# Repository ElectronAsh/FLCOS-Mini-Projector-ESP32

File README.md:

# FLCOS Mini Projector with ESP32 and Composite input.

WARNING: Please do not build this board yet. There are still some checks to do.

UPDATE: 29th April 2023: I finally bought one of the Jakks toy projectors from eBay US.
I hooked up the USB Logic Analyzer to the "SPI" bus on the projector's FLCOS module.
The projector only ever write to three registers after power-up, then another register to enable the FLCOS after a video signal is detected.

So I did a few tweaks to my Arduino code, and now my own board works, too. ;)

I also confirmed that the AliExpress FLCOS modules DO indeed work fine in the Jakks projector, so they are the same/compatible part.

There are still a few issues to sort out, where the FLCOS won't always turn on when you first plug USB power in, but it will work after pulling
the reset (EN_N) Low on the ESP32, or re-flashing via the Arduino IDE.

I've included a few photos below of the projector showing "Gex" on the 3DO.
This is a PAL 3DO, so I tweaked the Arduino code to fit the projected image better.
(the FLCOS registers will default to NTSC, so I tweaked the values for PAL.)

TODO...

Voltage reg pinouts and ADJ pins (use adjustable and add resistor dividers, or look for fixed-output regs for the BOM?)
FPC connector direction, top contact? (The FLCOS module will be mounted upside-down on the board)
Double-check the JST ZH pinout for the LEDs. DONE
Maybe change the pin header to some sort of socket for the Composite input? DONE
Check availability of all ICs on LCSC or Mouser, digikey etc. DONE
Hunt for parts, create a BOM. DONE
Run ERC and DRC. DONE
Order a few test PCBs. DONE

This is a driver board for the FLCOS mini projector modules on AliExpress...
https://www.aliexpress.com/item/1005003386129982.html

There is a forum post here, with the full datasheet for what appears to be the same FLCOS chip used on the AliExpress module.
https://whycan.com/t_2420.html

("datasheet" is actually the product brief. "cps" has all of the register settings.)

The pinout of the lower flex cable on post #4 of the forum seems to match up with the ribbon on the FLCOS module.

The pinout of the RGB LED cable on the module is a bit strange.
There is no correlation between the wire colours, the silkscreen designators, and the RGB LED chip itself.

I tested the RGB LED with a bench PSU, though, and the pinout on the Eagle schematic *should* be correct now.
I just need to double-check that the JST ZH connector for the LED is not rotated 180-degrees or something.

(it's possible the manufacturer changed the RGB LED for a different one on request, which is why the LED cable pinout doesn't seem to tally with the silkscreen?)

The exact maximum LED current is unknown.
I tested one of the Green LEDs with 160mA at first, and it didn't seem to increase in brightness much above 200mA.

The forward voltage drop of the Blue and Green LEDs was around 3.3 Volts, according to my bench PSU (when current-limiting). (there are two Green LEDs on the die) 

The forward voltage drop of the Red LED was around 2.0 Volts.

The included RGB LED has all of Anodes connected together.
I originally put some LM3404 LED driver ICs on the board, but they wouldn't have worked for a common-Anode RGB LED chip, so I changed those for the LM3414 instead.

The FLCOS module appears to be the same one used in the "JAKKS Eyeclops" toy projector...
https://videotechnology.blogspot.com/2010/11/inside-jakks-pacific-eyeclops-mini.html

Before I received some modules, I did a lot of tracing of the JAKKS PCB to try to confirm the pinout against the TVP5150 TV decoder chip.
The pinout seemed to match up with the forum post above.

There was a discussion on Twitter in 2021 about these modules, too...
https://twitter.com/AshEvans81/status/1498184526236987392?s=20&t=zDXLWlJON1HiXY-NYlLocg

The PCB layout was also discussed on the #lab channel of bitluni's Discord server.

bitluni's awesome ESP32 VGA output project was the reason I wanted to add an ESP32 to the board.
It could make for a neat mini movie player or similar (streaming low-res files from SD card.)

https://github.com/bitluni/ESP32Lib/blob/8f4b1bc9c331546c57c1ee837ac37303b8d8739c/examples/VGADemo14Bit/VGADemo14Bit.ino

(bitluni's code is untested with the FLCOS modules atm, but I think it will work OK with a few tweaks. The FLCOS chip accepts video input as sequential R,G,B bytes.)

I kept the TVP5150 chip on the board, as this is the same chip used in the JAKKS projector.
It outputs standard bt.656 style digital video, and accepts Composite input.

(The TVP5150 can receive both NTSC and PAL Composite, using one 14.318 MHz crystal.)

Only the TVP5150 or ESP32 can drive the FLCOS module at any one time.
The TVP chip can set it's output pins to High-Z (this is done via an I2C register), so it should be possible to keep both the ESP32 and TVP5150 onboard.

Most of the footprint libraries for the ESP32, SD slot, TVP5150, and LM3414 were taken from existing open-source projects.
I don't have the names or links to all of those projects now, but I will add them to the README if I can find them.

I used Eagle 9.0.1 to do the PCB layout.

Build at your own risk!

It does finally "work" now, in terms of getting Composite video to display.
But there are a few issues, as mentioned in the update at the top of this README.

I haven't tried generating video on the ESP32 yet, so I'm not 100% sure that will work without PCB changes.

ElectronAsh. ;)

This was a quick test of the Green LEDs. FLCOS chip itself is not powered.

Both Green LEDs in parallel, 220mA, lens was 150mm from the "screen".
The box is only 90mm wide.

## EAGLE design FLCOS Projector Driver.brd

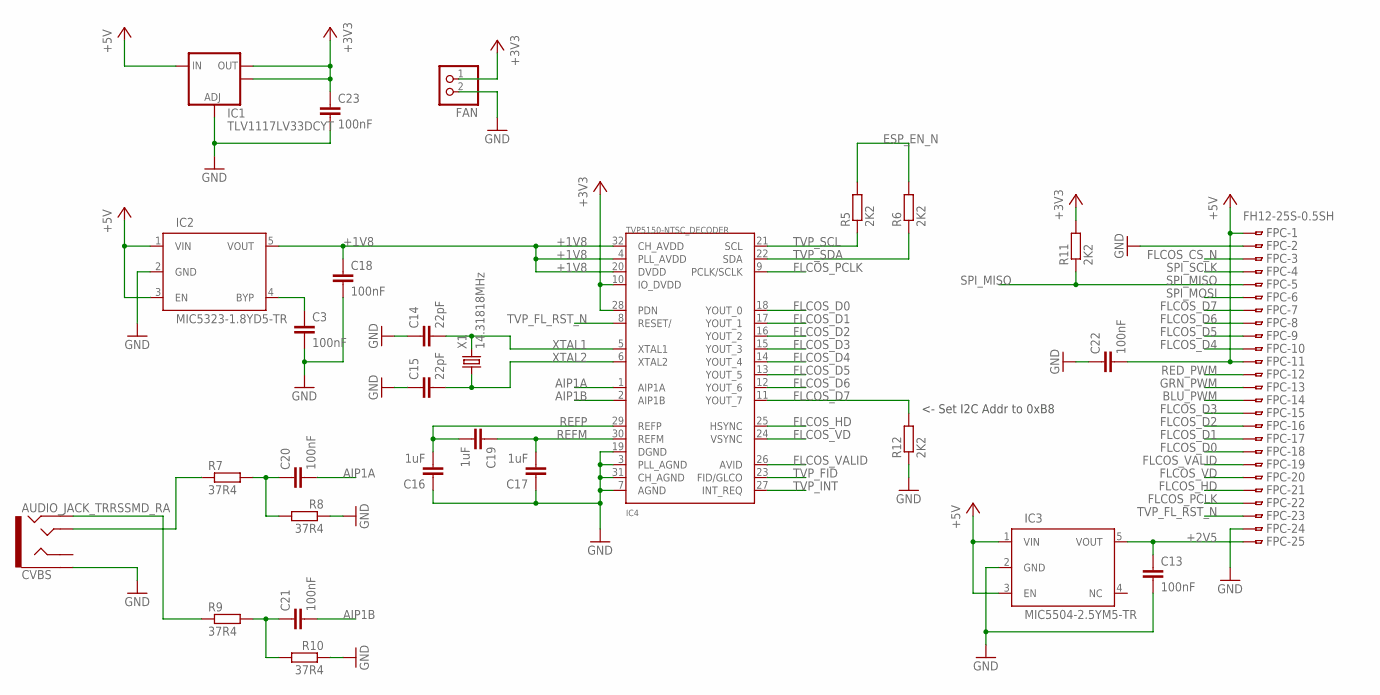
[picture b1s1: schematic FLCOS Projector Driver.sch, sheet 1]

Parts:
C3, C13, C18, C20, C21, C22, C23: 100nF; C0603
C14, C15: 22pF; C0603
C16, C17, C19: 1uF; C0603
CVBS: AUDIO_JACK_TRRSSMD_RA; AUDIO_JACK_3.5MM_TRRS_SMD_RA
FAN: JST_2PIN-THM; JST-PH-2-THM
FPC: FH12-25S-0.5SH
IC1: TLV1117LV33DCYT; SOT223
IC2: MIC5323-1.8YD5-TR; SOT23-5
IC3: MIC5504-2.5YM5-TR; SOT23-5
IC4: TVP5150-NTSC_DECODER; TQFP32-5MM
R5, R6, R11, R12: 2K2; R0603
R7, R8, R9, R10: 37R4; R0603
X1: 14.31818MHz; CTS406

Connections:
+1V8: C18.1, IC2.5 (VOUT), IC4.4 (PLL_AVDD), IC4.20 (DVDD), IC4.32 (CH_AVDD)
+2V5: C13.1, FPC.25, IC3.5 (VOUT)
+3V3: C23.1, FAN.1 (2), IC1.2 (OUT), IC1.4 (OUT), IC4.10 (IO_DVDD), IC4.28 (PDN), R11.2; also elsewhere on the board
+5V: C22.2, FPC.1, FPC.11, IC1.3 (IN), IC2.1 (VIN), IC2.3 (EN), IC3.1 (VIN), IC3.3 (EN); also elsewhere on the board
AIP1A: C20.2, IC4.1 (AIP1A)
AIP1B: C21.2, IC4.2 (AIP1B)
BLU_PWM: FPC.14; also elsewhere on the board
ESP_EN_N: R5.2, R6.2; also elsewhere on the board
FLCOS_CS_N: FPC.3; also elsewhere on the board
FLCOS_D0: FPC.18, IC4.18 (YOUT_0); also elsewhere on the board
FLCOS_D1: FPC.17, IC4.17 (YOUT_1); also elsewhere on the board
FLCOS_D2: FPC.16, IC4.16 (YOUT_2); also elsewhere on the board
FLCOS_D3: FPC.15, IC4.15 (YOUT_3); also elsewhere on the board
FLCOS_D4: FPC.10, IC4.14 (YOUT_4); also elsewhere on the board
FLCOS_D5: FPC.9, IC4.13 (YOUT_5); also elsewhere on the board
FLCOS_D6: FPC.8, IC4.12 (YOUT_6); also elsewhere on the board
FLCOS_D7: FPC.7, IC4.11 (YOUT_7), R12.2; also elsewhere on the board
FLCOS_HD: FPC.21, IC4.25 (HSYNC); also elsewhere on the board
FLCOS_PCLK: FPC.22, IC4.9 (PCLK/SCLK); also elsewhere on the board
FLCOS_VALID: FPC.19, IC4.26 (AVID); also elsewhere on the board
FLCOS_VD: FPC.20, IC4.24 (VSYNC); also elsewhere on the board
GND: C3.2, C13.2, C14.1, C15.1, C16.1, C17.1, C18.2, C22.1, C23.2, CVBS.EARTH, FAN.2 (1), FPC.2, FPC.24, IC1.1 (ADJ), IC2.2 (GND), IC3.2 (GND), IC4.3 (PLL_AGND), IC4.7 (AGND), IC4.19 (DGND), IC4.31 (CH_AGND), R8.1, R10.1, R12.1; also elsewhere on the board
GRN_PWM: FPC.13; also elsewhere on the board
unnamed: C3.1, IC2.4 (BYP)
unnamed: C21.1, R9.2, R10.2
unnamed: C20.1, R7.2, R8.2
unnamed: CVBS.TIP, R7.1
unnamed: CVBS.RING2, R9.1
RED_PWM: FPC.12; also elsewhere on the board
REFM: C17.2, C19.1, IC4.30 (REFM)
REFP: C16.2, C19.2, IC4.29 (REFP)
SPI_MISO: FPC.5, R11.1; also elsewhere on the board
SPI_MOSI: FPC.6; also elsewhere on the board
SPI_SCLK: FPC.4; also elsewhere on the board
TVP_FID: IC4.23 (FID/GLCO); also elsewhere on the board
TVP_FL_RST_N: FPC.23, IC4.8 (RESET/); also elsewhere on the board
TVP_INT: IC4.27 (INT_REQ); also elsewhere on the board
TVP_SCL: IC4.21 (SCL), R5.1; also elsewhere on the board
TVP_SDA: IC4.22 (SDA), R6.1; also elsewhere on the board
XTAL1: C14.2, IC4.5 (XTAL1), X1.3 (2)
XTAL2: C15.2, IC4.6 (XTAL2), X1.1

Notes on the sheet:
<- Set I2C Addr to 0xB8

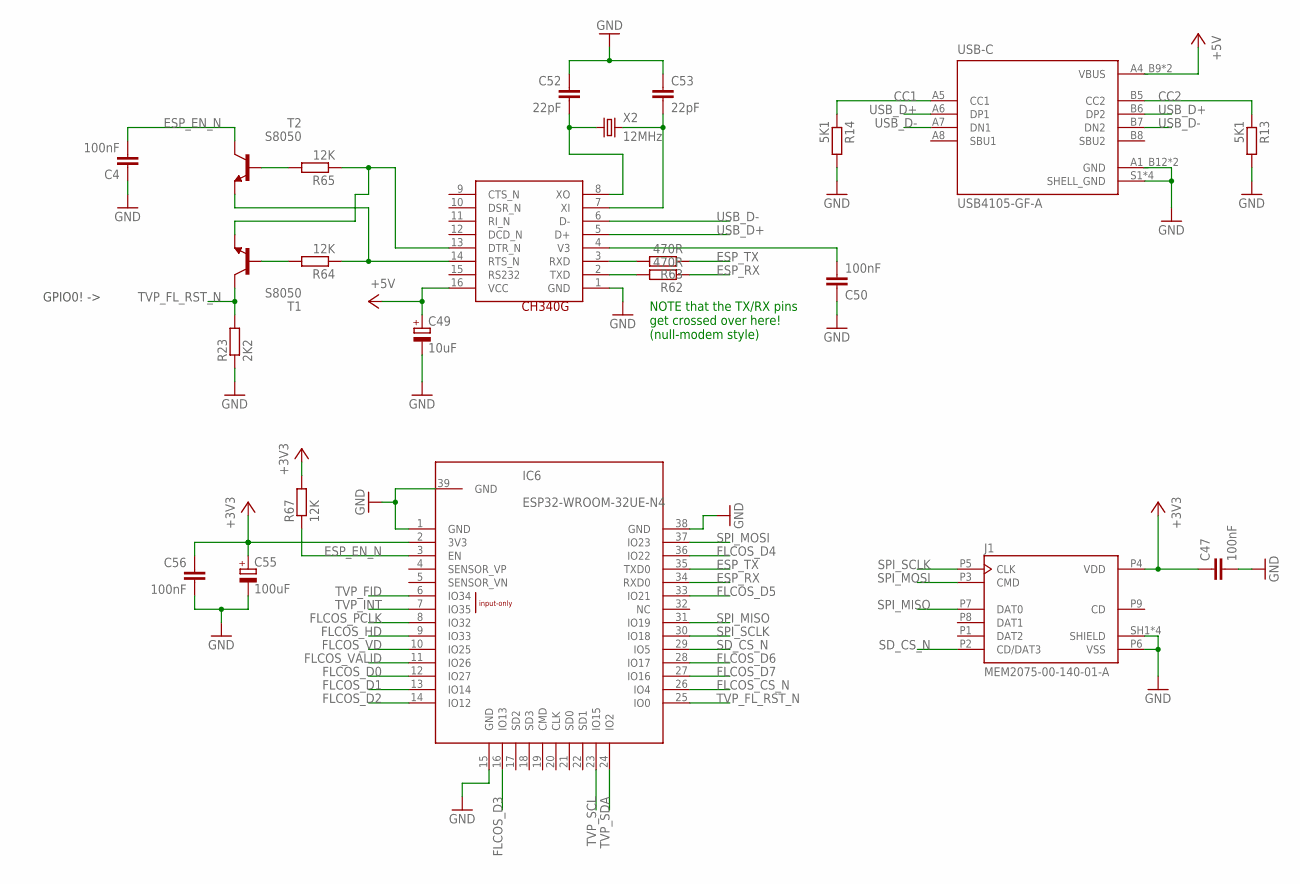
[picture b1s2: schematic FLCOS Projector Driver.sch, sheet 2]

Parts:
C4, C47, C50, C56: 100nF; C0603
C49: 10uF; B/3528-21W
C52, C53: 22pF; C0603
C55: 100uF; C/6032-28R
IC5: CH340G; SOIC16
IC6: ESP32-WROOM-32UE-N4; ESP32WROOM32D
J1: MEM2075-00-140-01-A; GCT_MEM2075-00-140-01-A
R13, R14: 5K1; R0603
R23: 2K2; R0603
R62, R63: 470R; R0603
R64, R65, R67: 12K; R0603
T1, T2: S8050; SOT23-BEC
USB-C: USB4105-GF-A; GCT_USB4105-GF-A
X2: 12MHz; CTS406

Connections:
+3V3: C47.1, C55.+, C56.1, IC6.2 (3V3), J1.P4 (VDD), R67.2; also elsewhere on the board
+5V: C49.+, IC5.16 (VCC), USB-C.A4_B9 (VBUS), USB-C.B4_A9 (VBUS); also elsewhere on the board
CC1: R14.1, USB-C.A5 (CC1)
CC2: R13.1, USB-C.B5 (CC2)
ESP_EN_N: C4.2, IC6.3 (EN), R67.1, T2.C; also elsewhere on the board
ESP_RX: IC6.34 (RXD0), R62.1
ESP_TX: IC6.35 (TXD0), R63.1
FLCOS_CS_N: IC6.26 (IO4); also elsewhere on the board
FLCOS_D0: IC6.12 (IO27); also elsewhere on the board
FLCOS_D1: IC6.13 (IO14); also elsewhere on the board
FLCOS_D2: IC6.14 (IO12); also elsewhere on the board
FLCOS_D3: IC6.16 (IO13); also elsewhere on the board
FLCOS_D4: IC6.36 (IO22); also elsewhere on the board
FLCOS_D5: IC6.33 (IO21); also elsewhere on the board
FLCOS_D6: IC6.28 (IO17); also elsewhere on the board
FLCOS_D7: IC6.27 (IO16); also elsewhere on the board
FLCOS_HD: IC6.9 (IO33); also elsewhere on the board
FLCOS_PCLK: IC6.8 (IO32); also elsewhere on the board
FLCOS_VALID: IC6.11 (IO26); also elsewhere on the board
FLCOS_VD: IC6.10 (IO25); also elsewhere on the board
GND: C4.1, C47.2, C49.-, C50.1, C52.1, C53.1, C55.-, C56.2, IC5.1 (GND), IC6.1 (GND), IC6.15 (GND), IC6.38 (GND), IC6.39 (GND), J1.P6 (VSS), J1.SH1 (SHIELD), J1.SH2 (SHIELD), J1.SH3 (SHIELD), J1.SH4 (SHIELD), R13.2, R14.2, R23.1, USB-C.A1_B12 (GND), USB-C.B1_A12 (GND), USB-C.S1 (SHELL_GND), USB-C.S2 (SHELL_GND), USB-C.S3 (SHELL_GND), USB-C.S4 (SHELL_GND); also elsewhere on the board
unnamed: IC5.2 (TXD), R62.2
unnamed: IC5.3 (RXD), R63.2
unnamed: R64.2, T1.B
unnamed: R65.2, T2.B
unnamed: IC5.14 (RTS_N), R64.1, T2.E
unnamed: IC5.13 (DTR_N), R65.1, T1.E
unnamed: C50.2, IC5.4 (V3)
unnamed: C53.2, IC5.7 (XI), X2.3 (2)
unnamed: C52.2, IC5.8 (XO), X2.1
SD_CS_N: IC6.29 (IO5), J1.P2 (CD/DAT3)
SPI_MISO: IC6.31 (IO19), J1.P7 (DAT0); also elsewhere on the board
SPI_MOSI: IC6.37 (IO23), J1.P3 (CMD); also elsewhere on the board
SPI_SCLK: IC6.30 (IO18), J1.P5 (CLK); also elsewhere on the board
TVP_FID: IC6.6 (IO34); also elsewhere on the board
TVP_FL_RST_N: IC6.25 (IO0), R23.2, T1.C; also elsewhere on the board
TVP_INT: IC6.7 (IO35); also elsewhere on the board
TVP_SCL: IC6.23 (IO15); also elsewhere on the board
TVP_SDA: IC6.24 (IO2); also elsewhere on the board
USB_D+: IC5.5 (D+), USB-C.A6 (DP1), USB-C.B6 (DP2)
USB_D-: IC5.6 (D-), USB-C.A7 (DN1), USB-C.B7 (DN2)

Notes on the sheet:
NOTE that the TX/RX pins get crossed over here! (null-modem style)
GPIO0! ->

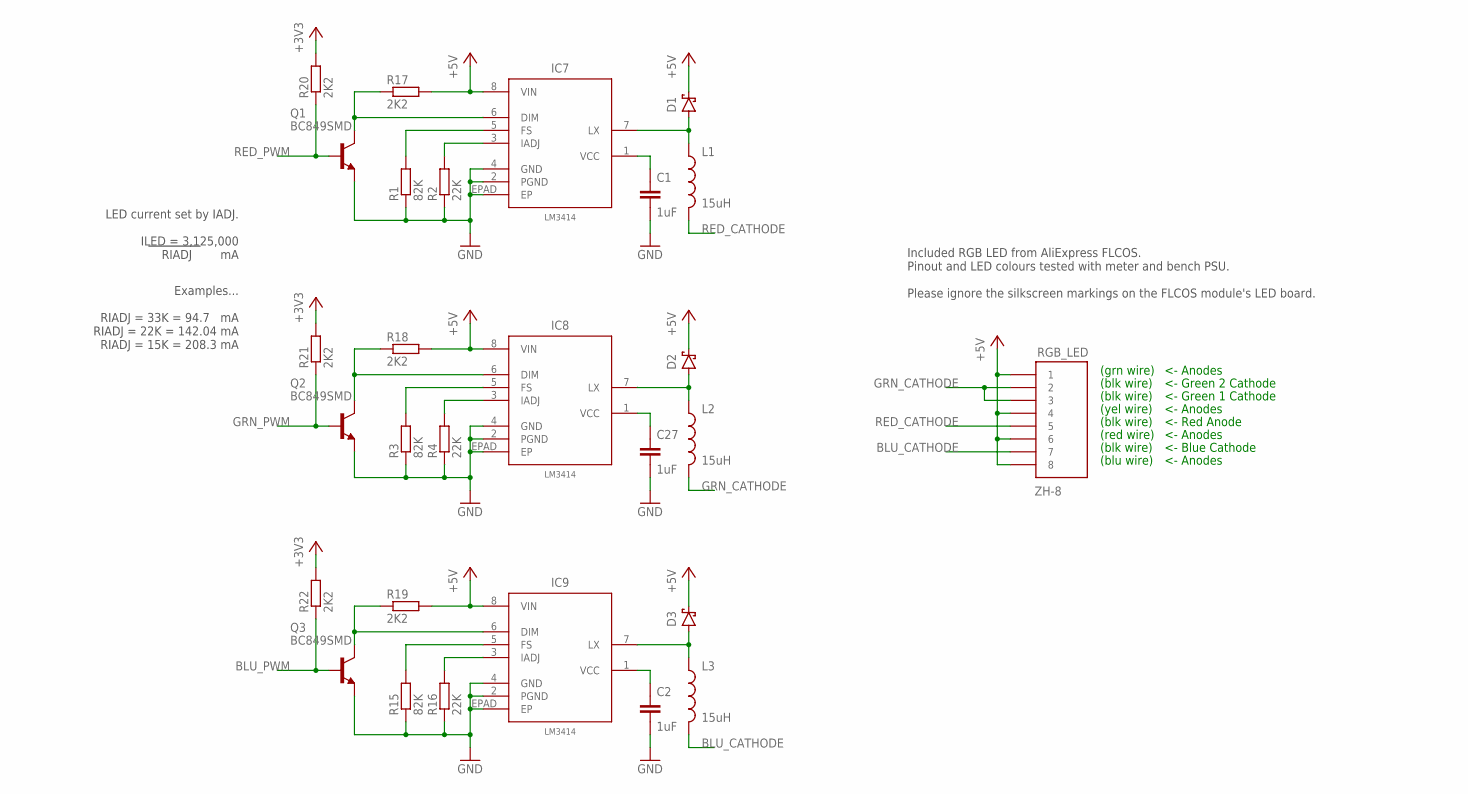
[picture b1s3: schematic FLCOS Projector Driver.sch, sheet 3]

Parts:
C1, C2, C27: 1uF; C0603
D1, D2, D3: "SB34AFC-AU_R1_000A1 SB34AFC-AU_R1_000A1"; SMA-DIODE-SCHOTTKY
IC7, IC8, IC9: LM3414; SO08-PAD
L1, L2, L3: 15uH; TAIYO-YUDEN-6X6X2.8
Q1, Q2, Q3: BC849SMD; SOT23-BEC
R1, R3, R15: 82K; R0603
R2, R4, R16: 22K; R0603
R17, R18, R19, R20, R21, R22: 2K2; R0603
RGB_LED: ZH-8

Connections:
+3V3: R20.2, R21.2, R22.2; also elsewhere on the board
+5V: D1.C, D2.C, D3.C, IC7.8 (VIN), IC8.8 (VIN), IC9.8 (VIN), R17.2, R18.2, R19.2, RGB_LED.1, RGB_LED.4, RGB_LED.6, RGB_LED.8; also elsewhere on the board
BLU_CATHODE: L3.2, RGB_LED.7
BLU_PWM: Q3.B, R22.1; also elsewhere on the board
GND: C1.2, C2.2, C27.2, IC7.2 (PGND), IC7.4 (GND), IC7.EPAD (EP), IC8.2 (PGND), IC8.4 (GND), IC8.EPAD (EP), IC9.2 (PGND), IC9.4 (GND), IC9.EPAD (EP), Q1.E, Q2.E, Q3.E, R1.1, R2.1, R3.1, R4.1, R15.1, R16.1; also elsewhere on the board
GRN_CATHODE: L2.2, RGB_LED.2, RGB_LED.3
GRN_PWM: Q2.B, R21.1; also elsewhere on the board
unnamed: IC7.6 (DIM), Q1.C, R17.1
unnamed: IC7.3 (IADJ), R2.2
unnamed: IC7.5 (FS), R1.2
unnamed: C1.1, IC7.1 (VCC)
unnamed: D1.A, IC7.7 (LX), L1.1
unnamed: IC9.3 (IADJ), R16.2
unnamed: IC9.5 (FS), R15.2
unnamed: C2.1, IC9.1 (VCC)
unnamed: D3.A, IC9.7 (LX), L3.1
unnamed: IC8.6 (DIM), Q2.C, R18.1
unnamed: IC9.6 (DIM), Q3.C, R19.1
unnamed: IC8.3 (IADJ), R4.2
unnamed: IC8.5 (FS), R3.2
unnamed: C27.1, IC8.1 (VCC)
unnamed: D2.A, IC8.7 (LX), L2.1
RED_CATHODE: L1.2, RGB_LED.5
RED_PWM: Q1.B, R20.1; also elsewhere on the board

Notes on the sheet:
(grn wire)
(blk wire)
(yel wire)
(red wire)
(blu wire)
<- Blue Cathode
<- Green 1 Cathode
<- Green 2 Cathode
<- Anodes
<- Red Anode
Included RGB LED from AliExpress FLCOS. Pinout and LED colours tested with meter and bench PSU. Please ignore the silkscreen markings on the FLCOS module's LED board.
LED current set by IADJ. ILED = 3,125,000 RIADJ mA
Examples... RIADJ = 33K = 94.7 mA RIADJ = 22K = 142.04 mA RIADJ = 15K = 208.3 mA

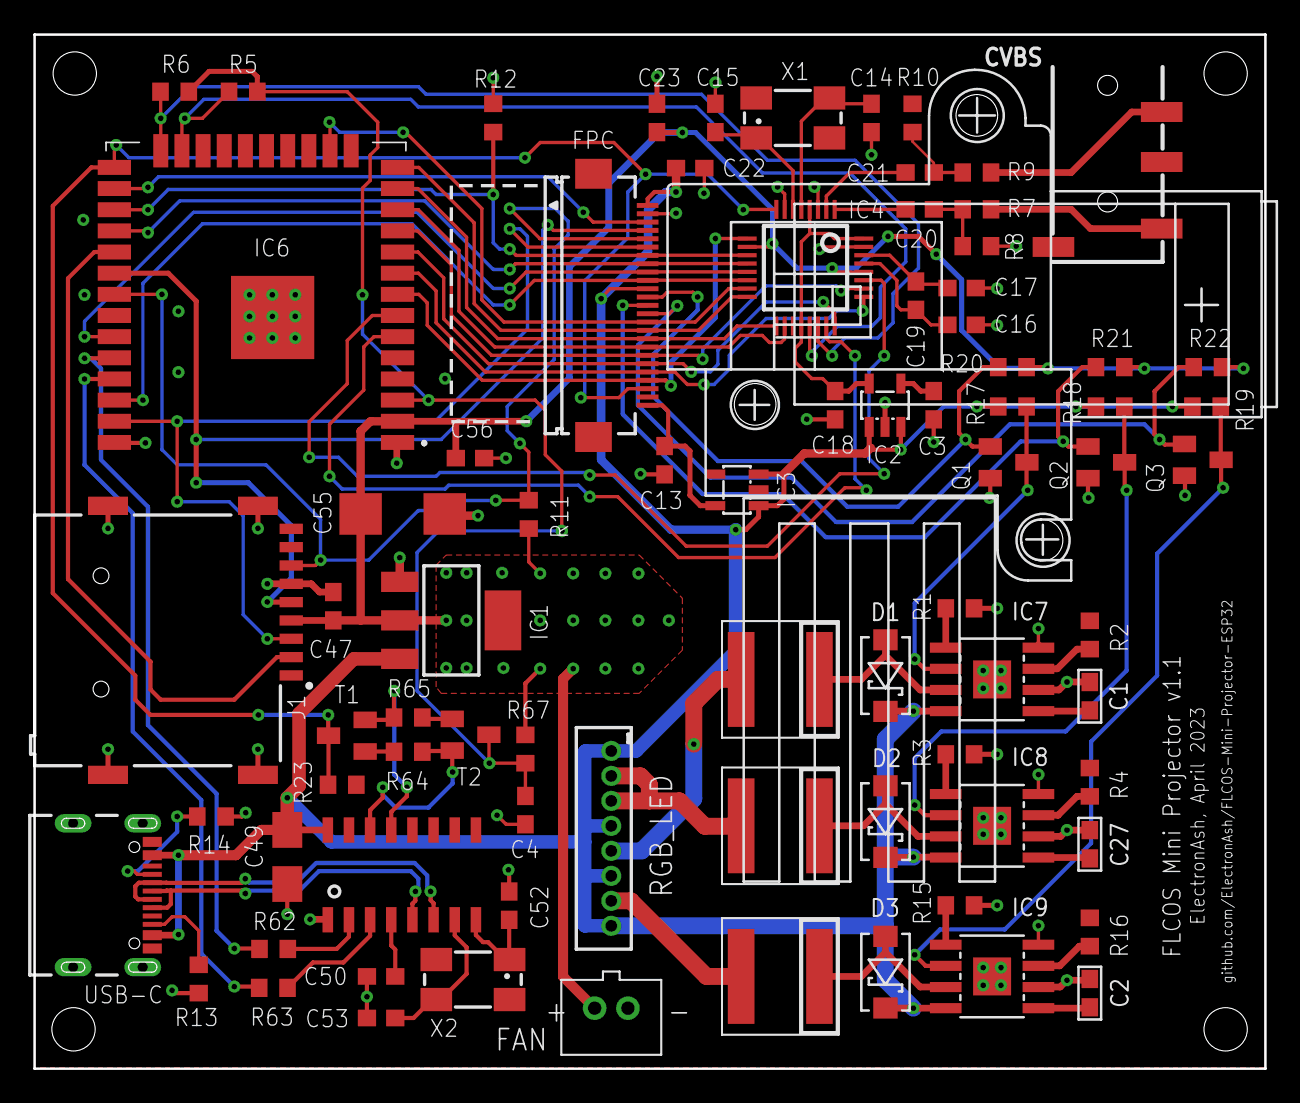
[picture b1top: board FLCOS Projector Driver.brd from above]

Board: 2 copper layers, 73.9 x 62.1 mm, 80 parts (0 on the bottom side), 75 nets.

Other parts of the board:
U$2: FLCOS_PROJ_OUTLINE

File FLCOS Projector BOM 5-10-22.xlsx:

Part | Quantity | Value | Device | Package | Description | MOUSER_PRICE | LINE_PRICE | MANUFACTURER_NAME | MANUFACTURER_PART_NUMBER | MOUSER_PART_NUMBER | LINK
C1, C2, C16, C17, C19, C27 | 6 | 1uF | CAPACITOR-CERAMICC0603 | C0603 | CAPACITOR, European symbol | 0.1 | 0.60000000000000009 | Samsung | CL10B105KA8NNNL | 187-CL10B105KA8NNNL | https://www.mouser.com/ProductDetail/Samsung-Electro-Mechani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
C3, C13, C18, C20, C21, C22, C23, C47, C50, C56 | 10 | 100nF | C-EUC0603 | C0603 | CAPACITOR, European symbol | 0.1 | 1 | Samsung | CL10B104MA8NNWC | 187-CL10B104MA8NNWC | https://www.mouser.com/ProductDetail/Samsung-Electro-Mechani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
C14, C15, C52, C53 | 4 | 22pF | C-EUC0603 | C0603 | CAPACITOR, European symbol | 0.1 | 0.4 | Samsung | CL10C220JB8NNWC CL10C220JB8NNWC | 187-CL10C220JB8NNWC | https://www.mouser.com/ProductDetail/Samsung-Electro-Mechani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
C49 | 1 | 10uF | CPOL-EUB/3528-21W | B/3528-21W | POLARIZED CAPACITOR, European symbol | 0.37 | 0.37 | Kyocera AVX | TAJB106M016RNJ | 581-TAJB106M016R | https://www.mouser.com/ProductDetail/KYOCERA-AVX/TAJB106M016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
C55 | 1 | 100uF | CPOL-EUC/6032-28R | C/6032-28R | POLARIZED CAPACITOR, European symbol | 0.67 | 0.67 | Kyocera AVX | TAJC107K006SNJ | 581-TAJC107K006SNJ | https://www.mouser.com/ProductDetail/KYOCERA-AVX/TAJC107K006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
 |  |  |  |  |  |  | 0
R1, R3, R15 | 3 | 82K | RESISTORR0603 | R0603 | RESISTOR, American symbol | 0.1 | 0.30000000000000004 | YAGEO | RT0603DRE0782KL | 603-RT0603DRE0782KL | https://www.mouser.com/ProductDetail/YAGEO/RT0603DRE0782KL?q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
R2, R4, R13, R14, R16 | 5 | 22K | RESISTORR0603 | R0603 | RESISTOR, American symbol | 0.12 | 0.6 | YAGEO | RT0603DRE0722KL | 603-RT0603DRE0722KL | https://www.mouser.com/ProductDetail/YAGEO/RT0603DRE0722KL?q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
R5, R6, R12, R67 | 4 | 2K2 | R-EU_R0603 | R0603 | RESISTOR, European symbol | 0.11 | 0.44 | YAGEO | RT0603DRE072K2L | 603-RT0603DRE072K2L | https://www.mouser.com/ProductDetail/YAGEO/RT0603DRE072K2L?q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
R7, R8, R9, R10, R11 | 5 | 37R4 | R-EU_R0603 | R0603 | RESISTOR, European symbol | 0.1 | 0.5 | YAGEO | RC0603FR-0737R4L | 603-RC0603FR-0737R4L | https://www.mouser.com/ProductDetail/YAGEO/RC0603FR-0737R4L?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
R62, R63 | 2 | 470R | R-EU_R0603 | R0603 | RESISTOR, European symbol | 0.1 | 0.2 | YAGEO | RT0603FRE07470RL | 603-RT0603FRE07470RL | https://www.mouser.com/ProductDetail/YAGEO/RT0603FRE07470RL?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
R64, R65 | 2 | 12K | R-EU_R0603 | R0603 | RESISTOR, European symbol | 0.1 | 0.2 | YAGEO | RT0603FRE0712KL | 603-RT0603FRE0712KL | https://www.mouser.com/ProductDetail/YAGEO/RT0603FRE0712KL?q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
 |  |  |  |  |  |  | 0
L1, L2, L3 | 3 | 15uH | INDUCTOR-TAIYO-YUDEN-6X2.8 | TAIYO-YUDEN-6X6X2.8 | Inductors | 5.2999999999999999E-2 | 0.159 | Laird | TYS6028150M-10 | 875-TYS6028150M-10 | https://www.mouser.com/ProductDetail/Laird-Performance-Mater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
 |  |  |  |  |  |  | 0
D1, D2, D3 | 3 | SCHOTTKY | DIODE-SCHOTTKYSMA | SMA-DIODE-SCHOTTKY | Schottky diodes in SFE's production catalog | 0.45 | 1.35 | Panjit | SB34AFC-AU_R1_000A1 SB34AFC-AU_R1_000A1 | 241-SB34AFCAUR1000A1 | https://www.mouser.com/ProductDetail/Panjit/SB34AFC-AU_R1_00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
T1, T2 | 2 | S8050 | BC846 | SOT23 | NPN TRANSISTOR | 0.21 | 0.42 | MCC | MMSS8050-H-TP | 833-MMSS8050-H-TP | https://www.mouser.com/ProductDetail/Micro-Commercial-Compon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
 |  |  |  |  |  |  | 0
IC1 | 1 | TLV1117LV33DCYT | V_REG_LM1117SOT223 | SOT223 | Voltage Regulator TLV1117. 1 Amp. Pos. | 1.1399999999999999 | 1.1399999999999999 | Texas Instruments | TLV1117LV33DCYT | 595-TLV1117LV33DCYT | https://www.mouser.com/ProductDetail/Texas-Instruments/TLV11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
IC2 | 1 | MIC5323-1.8YD5-TR | MIC5323-1.8YD5-TR | SOT23-5 | VOLTAGE REGULATOR | 0.68 | 0.68 | Microchip | MIC5323-1.8YD5-TR | 998-MIC5323-1.8YD5TR | https://www.mouser.com/ProductDetail/Microchip-Technology-At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
IC3 | 1 | MIC5504-2.5YM5-TR | MIC5504-2.5YM5-TR | SOT23-5 | VOLTAGE REGULATOR | 0.16 | 0.16 | Microchip | MIC5504-2.5YM5-TR | 998-MIC5504-2.5YM5TR | https://www.mouser.com/ProductDetail/Microchip-Technology-At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
IC7, IC8, IC9 | 3 | LM3414 | LM3414SO08-PAD | SO08-PAD |  | 2.48 | 7.4399999999999995 | Texas Instruments | LM3414HVMR/NOPB | 926-LM3414HVMR/NOPB | https://www.mouser.com/ProductDetail/Texas-Instruments/LM341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
 |  |  |  |  |  |  | 0
IC4 | 1 | TVP5150-NTSC_DECODER | TVP5150-NTSC_DECODER | TQFP32-5MM | Texas Instruments NTSC/PAL Decoder | 6.56 | 6.56 | Texas Instruments | TVP5150AM1PBSR | 595-TVP5150AM1PBSR | https://www.mouser.com/ProductDetail/Texas-Instruments/TVP51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
IC6 | 1 | ESP32-WROOM-32UE-N4 | ESP32-WROOM-32UE-N4 | ESP32WROOM32D | ESP32-D0WD, 4Mbits SPI flash, U.FL antenna | 3 | 3 | Espressif | ESP32-WROOM-32UE-N4 | 356-ESP32WRM32UE32UH | https://www.mouser.com/ProductDetail/Espressif-Systems/ESP32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
 |  |  |  |  |  |  | 0
J1 | 1 | MICROSD | MICROSD | C12075 | Micro-SD / Transflash card holder with SPI pinout | 1.96 | 1.96 | GCT | MEM2075-00-140-01-A MEM2075-00-140-01-A | 640-MEM20750014001A | https://www.mouser.com/ProductDetail/GCT/MEM2075-00-140-01-A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
USB-C | 1 | USB4105-GF-A | USB Type C,2.0 | GCT_USB4105-GF-A | USB-C connector | 0.56000000000000005 | 0.56000000000000005 | GCT | USB4105-GF-A | 640-USB4105-GF-A | https://www.mouser.com/ProductDetail/GCT/USB4105-GF-A?qs=KUo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
FPC | 1 | FH12-25S-0.5SH | FH12-25S-0.5SH | FH12-25S-0.5SH | 0.5mm Pitch Connectors For FPC/FFC | 0.81 | 0.81 |  | SFV25R-2STE1HLF | 649-SFV25R-2STE1HLF | https://www.mouser.com/ProductDetail/Amphenol-FCI/SFV25R-2ST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
 |  |  |  |  |  |  | 0
X1 | 1 | 14.31818MHz | CRYSTALCTS406 | CTS406 | CRYSTAL | 1.1299999999999999 | 1.1299999999999999 | ECS | ECS-143-20-23A-EN-TR | 520-ECS143-20-23A-EN | https://www.mouser.com/ProductDetail/ECS/ECS-143-20-23A-EN-T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
X2 | 1 | 12MHz | CRYSTALCTS406 | CTS406 | CRYSTAL | 0.37 | 0.37 | ECS | ECS-120-12-36-AGN-TR3 | 520-120-12-36AGN-TR3 ECS-120-12-36-AGN-TR3 | https://www.mouser.com/ProductDetail/ECS/ECS-120-12-36-AGN-T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
 |  |  |  |  |  |  | 0
CVBS | 1 | AUDIO_JACK_TRRSSMD_RA | AUDIO_JACK_TRRSSMD_RA | 1X03 | Audio Jack 3.5mm TRRS | 0.95 | 0.95 | Sparkfun | PRT-12639 | 474-PRT-12639 | https://www.mouser.com/ProductDetail/SparkFun/PRT-12639?qs=W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
 |  |  |  |  |  |  | 0
 |  |  |  |  |  |  | 0
IC5 | 1 | CH340G | CH340G | SOIC16 | USB UART IC. SOIC16 package. | 0 | 0 |  | CH340G |  | Not commonly available from western distributors. May need to buy on eBay, Amaz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
RGB | 1 | ZH-8 | ZH-8 | ZH-8 | JST ZH connector. 8-pin. 1.5mm pitch. | 0 | 0 | JST | JST ZH 8-pin |  | Not commonly available from western distributors. May need to buy on eBay, Amaz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
 |  |  |  |  |  |  | 0
PCB | 1 | PCB | PCB | PCB | 2-layer | 0.497 | 0.497 | JLCPCB |  |  | Price based on cost of $4.97 for TEN PCBs on JLCPCB. 5th October 2022. Not incl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
Stencil | 1 | STENCIL | STENCIL | STENCIL | Solder paste stencil, metal | 6.95 | 6.95 | JLCPCB |  |  | Price based on $6.95 for ONE stencil on JLCPCB. 5th October 2022. Not including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
 |  |  |  |  |  | Total: | 39.415999999999997

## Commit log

2022-10-03 added README.md
2022-10-03 Add images to README
2022-10-03 trying to fix README images
2022-10-03 trying to fix README images 3
2022-10-03 added pullups to I2C
2022-10-03 RGB LED current set to 156mA
2022-10-03 schematic tweaks
2022-10-04 Allow USB/GPIO0 to reset TVP and FLCOS
2022-10-04 GPIO0 to reset the TVP, ESP_EN_N to reset the FLCOS
2022-10-04 README update
2022-10-04 Added pulldown on FL_D7, to set I2C Addr
2022-10-04 removed erroneous polys from tStop layer. Fixed 3V3 reg vias
2022-10-04 Started BOM. Changing parts to Mouser in-stock
2022-10-05 ERC and DRC passed. BOM not quite done
2022-10-05 Changed to USB-C. BOM passives not done yet
2022-10-05 Changed Composite pin header for TRRS socket
2022-10-05 Fixed FLCOS mounting hole position vs flex
2022-10-05 Proto PCBs and stencil ordered. Passives BOM not done
2022-10-06 XLSX BOM finished. Tweaked FLCOS mounting points
2022-10-06 Added Mouser cart XLS. BOM tweaks due to low stocks
2022-10-15 Changed R11 to a pull-up for FLCOS_SOUT
2023-04-29 Added Arduino ESP32 Project folder
2023-04-29 Added inverter transistors for RGB LED PWM signals
2023-04-29 PCB changes to fix auto-reset during Flash programming
2023-04-29 Added JST PH fan header
2023-04-29 Added images. Updated README
2023-04-29 Fixed README for images
2023-04-29 Fixed README for images (again)
2023-04-29 Added image of built board/projector
2023-04-29 Added images
2023-04-30 Updated image
2024-01-29 Fixed date in README update
2024-10-13 Fixed the CC 5K1 pull-down resistors on USB-C. They used to be 22K pull-ups!

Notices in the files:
parts and their libraries:
SparkFun-AnalogIC: Licensing: CC v3.0 Share-Alike You are welcome to use this library for commercial purposes.
SparkFun-Connectors: Licensing: Creative Commons ShareAlike 4.0 International - https://creativecommons.org/licenses/by-sa/4.0
